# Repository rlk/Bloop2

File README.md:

# Bloop2 — Dual Op-Amp Boosted Loop Switcher

Bloop2 is an effects loop switcher. It has Instrument Input and Amplifier Output jacks, plus effects loop Send and Return jacks with a single stomp button to switch that loop in or out.

Because it's often desirable to run the effects loop louder than the instrument signal, Bloop2 provides volume controls at both the Send and Return, with a maximum gain of around 10. When switched off, the circuit is fully bypassed.

- [Schematic PNG](etc/Bloop2-Schematic.png)
- [Schematic PDF](etc/Bloop2-Schematic.pdf)
- [Hammond 1590B Drill Template SVG](etc/Bloop2-Drill-Template.svg)
- [PCB Prerendering](etc/Bloop2-Render.jpeg)
- [Gerber Files](etc/gerber)

Finished photos:

- [Enclosure](etc/Bloop2-Enclosure.jpeg)
- [Guts](etc/Bloop2-Guts.jpeg)

## Design notes

- The overall structure uses a constant gain with a volume control at the output.
	- As opposed to a variable gain.
	- This makes attenuation possible with a non-inverting amplifier.
	- This also makes it possible to dial back noise.

- The schematic specifies a TL072, but any standard pin-out dual op amp will do.
	- Op amp selection will not make a significant difference in color, as this circuit remains squarely within the common mode when correctly powered.

- The voltage requirement is entirely determined by the op amp. 
	- I use a TLE2072 which is within spec at either V+ = 9V or 18V. 

- The PCB is sized and shaped to fit a Hammond 1590B.
	- The 1590B is 56mm wide overall, but only 44mm wide at the ends. Thus the cutouts.
	- The PCB is limited to 50mm x 50mm to fit the cheap option at [DirtyPCBs].

- The PCB layout dictates the pin pitch of the stomp switch.
	- The current design specifies an E-Switch FS57003PLT2B2M2QE, which has 5.3mm x 4.8mm pitch.

- D2 can be any Schottky larger than V+.
	- They tend to cost the same regardless of voltage.

- The LED is specified at V+ = 9V, Vf = 2.2V, If = 20mA.
	- RLED1 = (9.0 - 2.2) / 0.020 = 340Ω.
	- Watch out for over-current on your LED with higher V+.
		- Or don't. It's probably fine at 40mA.

- R1 = R2.
	- They form a voltage divider giving the reference voltage.

- C1 and C2 values are cargo-culted to 47uF from common designs.
	- These values are pretty arbitrary.
		- Though the circuit will take a moment to start up if too small.
	- They match C5 and C6 by coincidence. I guess this eases sourcing.

- The two channels are identical.
	- Component value selections should be consistent between the two.
	- Though it's rational for the maximum Output gain to be lower than the maximum Send gain, if desired, since the loop is usually hotter than the line and Send usually amplifies while Output attenuates.

- R3 and C3 form a high-pass filter on the input.
	- The 3dB point is 1 / (2π R3 C3) = 1.6Hz.

- R3 = R5.
	- As a rule, R5 >> R1.
	- It's not strictly necessary that R3 = R5, except that both applications call for large R, and I appreciate the symmetry whereby two distinct potentials are established on either side of C3.

- Gain is 1 + R9 / R7.
	- With R9 = 22K and R7 = 2.2K, voltage gain is 11.
	- Keep R7 and R9 low to eliminate noise. Effectively zero current flows here.

- C5 is needed to eliminate DC gain, but incurs a high-pass filter on the feedback.
	- The value is selected to impedance match R7 at a frequency well below the audio band.
	- The 3db point is 1 / (2π R7 C5) = 1.5Hz.
	- The motivation to keep R7 and R9 small leads to large C5 ([AoE] 4.2.2.A).

- C7 and RV1 form a high-pass filter on the output.
	- The 3dB point is 1 / (2π RV1 C7) = 1.6Hz.
	- Larger RV1 permits a smaller C7 if desired.
	- C7 need not be polar, but capacitor type seems to a have a significant impact on color here.

- Pin 3 of RV1 and RV2 must be grounded, but it's not strictly necessary to ground at the given PCB pad.

- The circuit and signal grounds are completely separate, as designed. You'll probably want to tie them together. This is most easily done off-board, by wiring the negative terminal of the power jack to the sleeve terminal of one of the audio jacks.

## Analysis

To measure the circuit's effect on the input, here are a few screenshots from my scope. These show one channel of the device acting on a 1Hz 1Vpp square wave. Channel 1 displays the Instrument Input, at the bottom, and channel 2 displays the Send output, at the top. The volume is tuned to unity. The two traces appear identical.

To see a difference, overlay the two traces, set an offset of -0.5V, and zoom in. The two traces clearly differ. The input is the flatter one. But they are within 10mV of one another, and environmental noise dominates at this scale.

To analyze the true effect of the circuit, compute the difference between the input and output, similarly zoomed. We see noise on the scale of 10mV peak-to-peak, centered on zero. Spikes appear at the transitions indicating a minor phase shift in the output. The difference, for the most part, remains near zero.

To quantify the effect, compute the running average of the difference to eliminate noise. This demonstrates a deviation from square that is indeed around 10mV, or 1% of the amplitude of the input.

The spike in the difference indicates a tiny phase shift in the output. Reducing the time interval lets us quantify it.

Smoothing shows this delay to be at most 1 microsecond, far below the audible band.

Performance of the other channel is effectively identical.

[AoE]: https://artofelectronics.net
[DirtyPCBs]: https://dirtypcbs.com

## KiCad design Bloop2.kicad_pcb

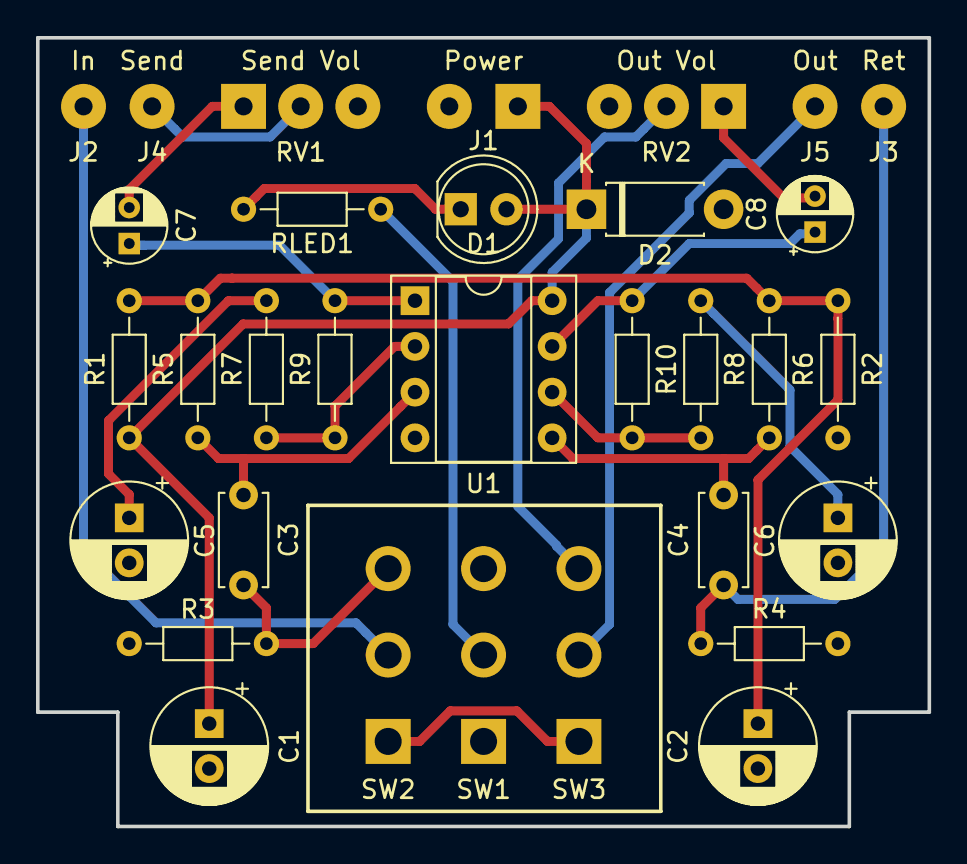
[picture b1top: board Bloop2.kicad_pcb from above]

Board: 2 copper layers, 49.5 x 43.8 mm, 32 parts (0 on the bottom side), 22 nets.

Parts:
C1, C2, C5, C6: 47u; CP_Radial_D6.3mm_P2.50mm
C3, C4: 1u; C_Disc_D5.0mm_W2.5mm_P5.00mm
C7, C8: 10u; CP_Radial_D4.0mm_P2.00mm
D1: LED; LED_D5.0mm
D2: 40V; D_DO-41_SOD81_P7.62mm_Horizontal
J1: Power In; SolderWirePad_1x02_P3.81mm_Drill1mm
J2: Input; SolderWirePad_1x01_Drill1mm
J3: Return; SolderWirePad_1x01_Drill1mm
J4: Send; SolderWirePad_1x01_Drill1mm
J5: Output; SolderWirePad_1x01_Drill1mm
R1, R2: 10k; R_Axial_DIN0204_L3.6mm_D1.6mm_P7.62mm_Horizontal
R3, R4, R5, R6: 100k; R_Axial_DIN0204_L3.6mm_D1.6mm_P7.62mm_Horizontal
R7, R8: 2k2; R_Axial_DIN0204_L3.6mm_D1.6mm_P7.62mm_Horizontal
R9, R10: 22k; R_Axial_DIN0204_L3.6mm_D1.6mm_P7.62mm_Horizontal
RLED1: 360; R_Axial_DIN0204_L3.6mm_D1.6mm_P7.62mm_Horizontal
RV1, RV2: 10k; SolderWirePad_1x03_P3.175mm_Drill1mm
SW1: 3PDTA; SolderWirePad_1x03_P9.60mm_Drill1.5mm
SW2: 3PDTB; SolderWirePad_1x03_P9.60mm_Drill1.5mm
SW3: 3PDTC; SolderWirePad_1x03_P9.60mm_Drill1.5mm
U1: TL072; DIP-8_W7.62mm_Socket

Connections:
+9V: C1.1, D1.2, D2.1, J1.1, R1.1, U1.8
BYPASS: SW2.1, SW3.1
GND: C1.2, C2.2, C5.2, C6.2, D2.2, J1.2, R2.2, R3.2, R4.2, RV1.3, RV2.3, SW1.3, U1.4
unnamed: C3.1, R5.1, U1.3
unnamed: C3.2, R3.1, SW2.3
unnamed: C4.1, R6.1, U1.5
unnamed: C4.2, J3.1, R4.1
unnamed: C5.1, R7.2
unnamed: C6.1, R8.2
unnamed: C7.1, R9.2, U1.1
unnamed: C7.2, RV1.1
unnamed: C8.1, R10.2, U1.7
unnamed: C8.2, RV2.1
unnamed: D1.1, RLED1.1
unnamed: J2.1, SW2.2
unnamed: J4.1, RV1.2
unnamed: J5.1, SW3.2
unnamed: R7.1, R9.1, U1.2
unnamed: R8.1, R10.1, U1.6
unnamed: RLED1.2, SW1.2
unnamed: RV2.2, SW3.3
VREF: C2.1, R1.2, R2.1, R5.2, R6.2

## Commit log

2019-02-28 Initial design of boosted loop switcher.
    A simple op-amp booster. Just putting some thoughts into a schematic.
2019-02-28 Feature complete device with first layout.
2019-02-28 Improved, compacted layout.
2019-02-28 Tuned layout.
    The moment you send a PCB off for printing, you think of a ton of obvious ideas for improvement.
2019-02-28 Fix design flaws detected in previous circuit.
    A previous design was printed and fabricated, revealing a number of problems.
    1. The pots were not appropriate for panel mounting. They were too short, leaving no room for the electrolitic capacitors.
    2. The switches were backwards on the schematic (easily resolvable in the wiring).
    3. The circuit cut the highs too much. This revision matches the input RC to the Timmy.
    This design mounts the footswitch on the PCB, which should give a secure enclosure mounting.
2019-03-04 Add Hammond 1590B drill template
2019-03-08 Add footprint for custom solder wire pad.
2019-03-08 Tweak LED resistor for selected LED.
2019-03-28 Add bias resistors. Overall shift toward more conservative design.
2019-03-28 Minor schematic layout tweaks.
2019-03-29 Tune component values.
2019-03-29 Add PDF of schematic
2019-03-29 Revert renaming TL072 to TLE2072.
    TLE2072 isn't in the library, so the net got scrambled.
2019-03-30 PCB layout draft
2019-03-30 Fix a few PCB labels
2019-03-31 Specify polar output caps.
    Output cap type seems to have a significant effect on EQ. I'd like to leave this as an option for the builder, but leaving the schematic symbols non-polarized results in a backwards footprint on the 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
2019-03-31 Add design notes and image.
2019-03-31 Fix broken image.
2019-03-31 Organize derived files in etc.
2019-03-31 Fix misnamed file
2019-03-31 Update schematic PDF
2019-03-31 Doc tweaks.
2019-04-12 Finalize notes and go to print
2019-04-13 Add images and organize
2019-04-13 Reduce JPEGs
2019-04-13 Remove images from README
2019-04-13 Link Gerber files from README
2019-04-13 Add description
2019-04-17 Add scope shots
2019-04-17 Fix scope images
2019-04-19 Add new scope screen shots.
2019-04-19 Update readme with more images
2019-04-20 README tweaks
2019-04-21 README formatting

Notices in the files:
Bloop2.kicad_pcb:
©2019 kooima.net
